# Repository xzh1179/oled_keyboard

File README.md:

# OLED Keyboard

A custom mechanical keyboard project featuring per-key OLED displays for dynamic legends, status information, and highly personalized layouts.

## Overview

OLED Keyboard is an experimental custom keyboard platform where each key can display its own icon, label, layer state, shortcut, or custom graphics.  
The goal of this project is to explore the intersection of keyboard design, multi-panel display integration, power distribution, and user interaction.

This project combines:

- custom PCB design
- embedded firmware development
- OLED display integration
- keyboard matrix scanning
- USB communication
- dynamic key rendering

Depending on the firmware mode, each key can show:

- key labels
- shortcuts
- symbols
- macros
- layer indicators
- application-specific legends
- simple animations or status feedback

## Motivation

Traditional keyboards are static: the legend printed on a keycap never changes.  
This project explores a more flexible and expressive approach where each key can adapt visually to:

- active layer
- language layout
- software context
- macro profile
- user preferences

The idea is to make a keyboard that is not only functional, but also programmable, informative, and visually unique.

## Features

- Per-key OLED displays
- Fully custom PCB
- Mechanical key switches
- Dynamic legends and layer indication
- Custom embedded firmware
- USB connectivity
- Macro and shortcut support
- Potential support for animations and contextual UI

## Hardware

Current hardware exploration includes:

- microcontroller: RP2040 
- OLED display 0.64inch 64x64 pixels, RGB color, based on SSD1357 controller 
- keyboard matrix scanning
- Kailh Choc V1 mechanical switch
- power distribution for many small displays
- SPI display communication
- optional rotary encoder support
- USB interface

> The exact hardware architecture may evolve as the project progresses.

## Architecture

The project is roughly divided into the following blocks:

1. **Keyboard matrix**  
   Detects key presses using rows and columns.

2. **Display subsystem**  
   Drives the OLED displays and refreshes per-key content.

3. **Firmware layer engine**  
   Handles keymaps, layers, macros, and display content generation.

4. **USB HID interface**  
   Sends keyboard events to the host computer.

5. **Power management**  
   Ensures stable power delivery for the MCU, switches, and all displays.

## Challenges

This project involves several interesting engineering challenges:

- driving many OLED displays efficiently
- balancing refresh rate and power consumption
- routing high-density display interconnects on PCB while keeping the layout compact, especially do not create too large space between two keys
- scaling SPI/I2C buses
- memory usage for icons/fonts/framebuffers
- firmware architecture for real-time input + rendering
- mechanical integration and assembly

## Project Status

This project is currently in active development.

Current focus areas include:

- hardware architecture exploration
- PCB design
- display driving strategy
- firmware prototyping
- validation of power and signal integrity constraints

## Repository Structure

```text
.
├── docs/            # Design notes, architecture, ideas, references
├── hardware/        # Schematics, PCB files, manufacturing outputs
├── firmware/        # Embedded firmware source code
├── images/          # Photos, renders, screenshots, diagrams
├── tools/           # Helper scripts, generators, utilities
└── README.md
```

## Assembly
The initial assembly of the keyboard is shown in the two figures below. At this stage, only one screen and one mechanical switch were mounted 
in order to validate the basic functionalities before proceeding with the soldering of the remaining components.

Initial assembly has been completed. Functional testing will be conducted in the next stage.

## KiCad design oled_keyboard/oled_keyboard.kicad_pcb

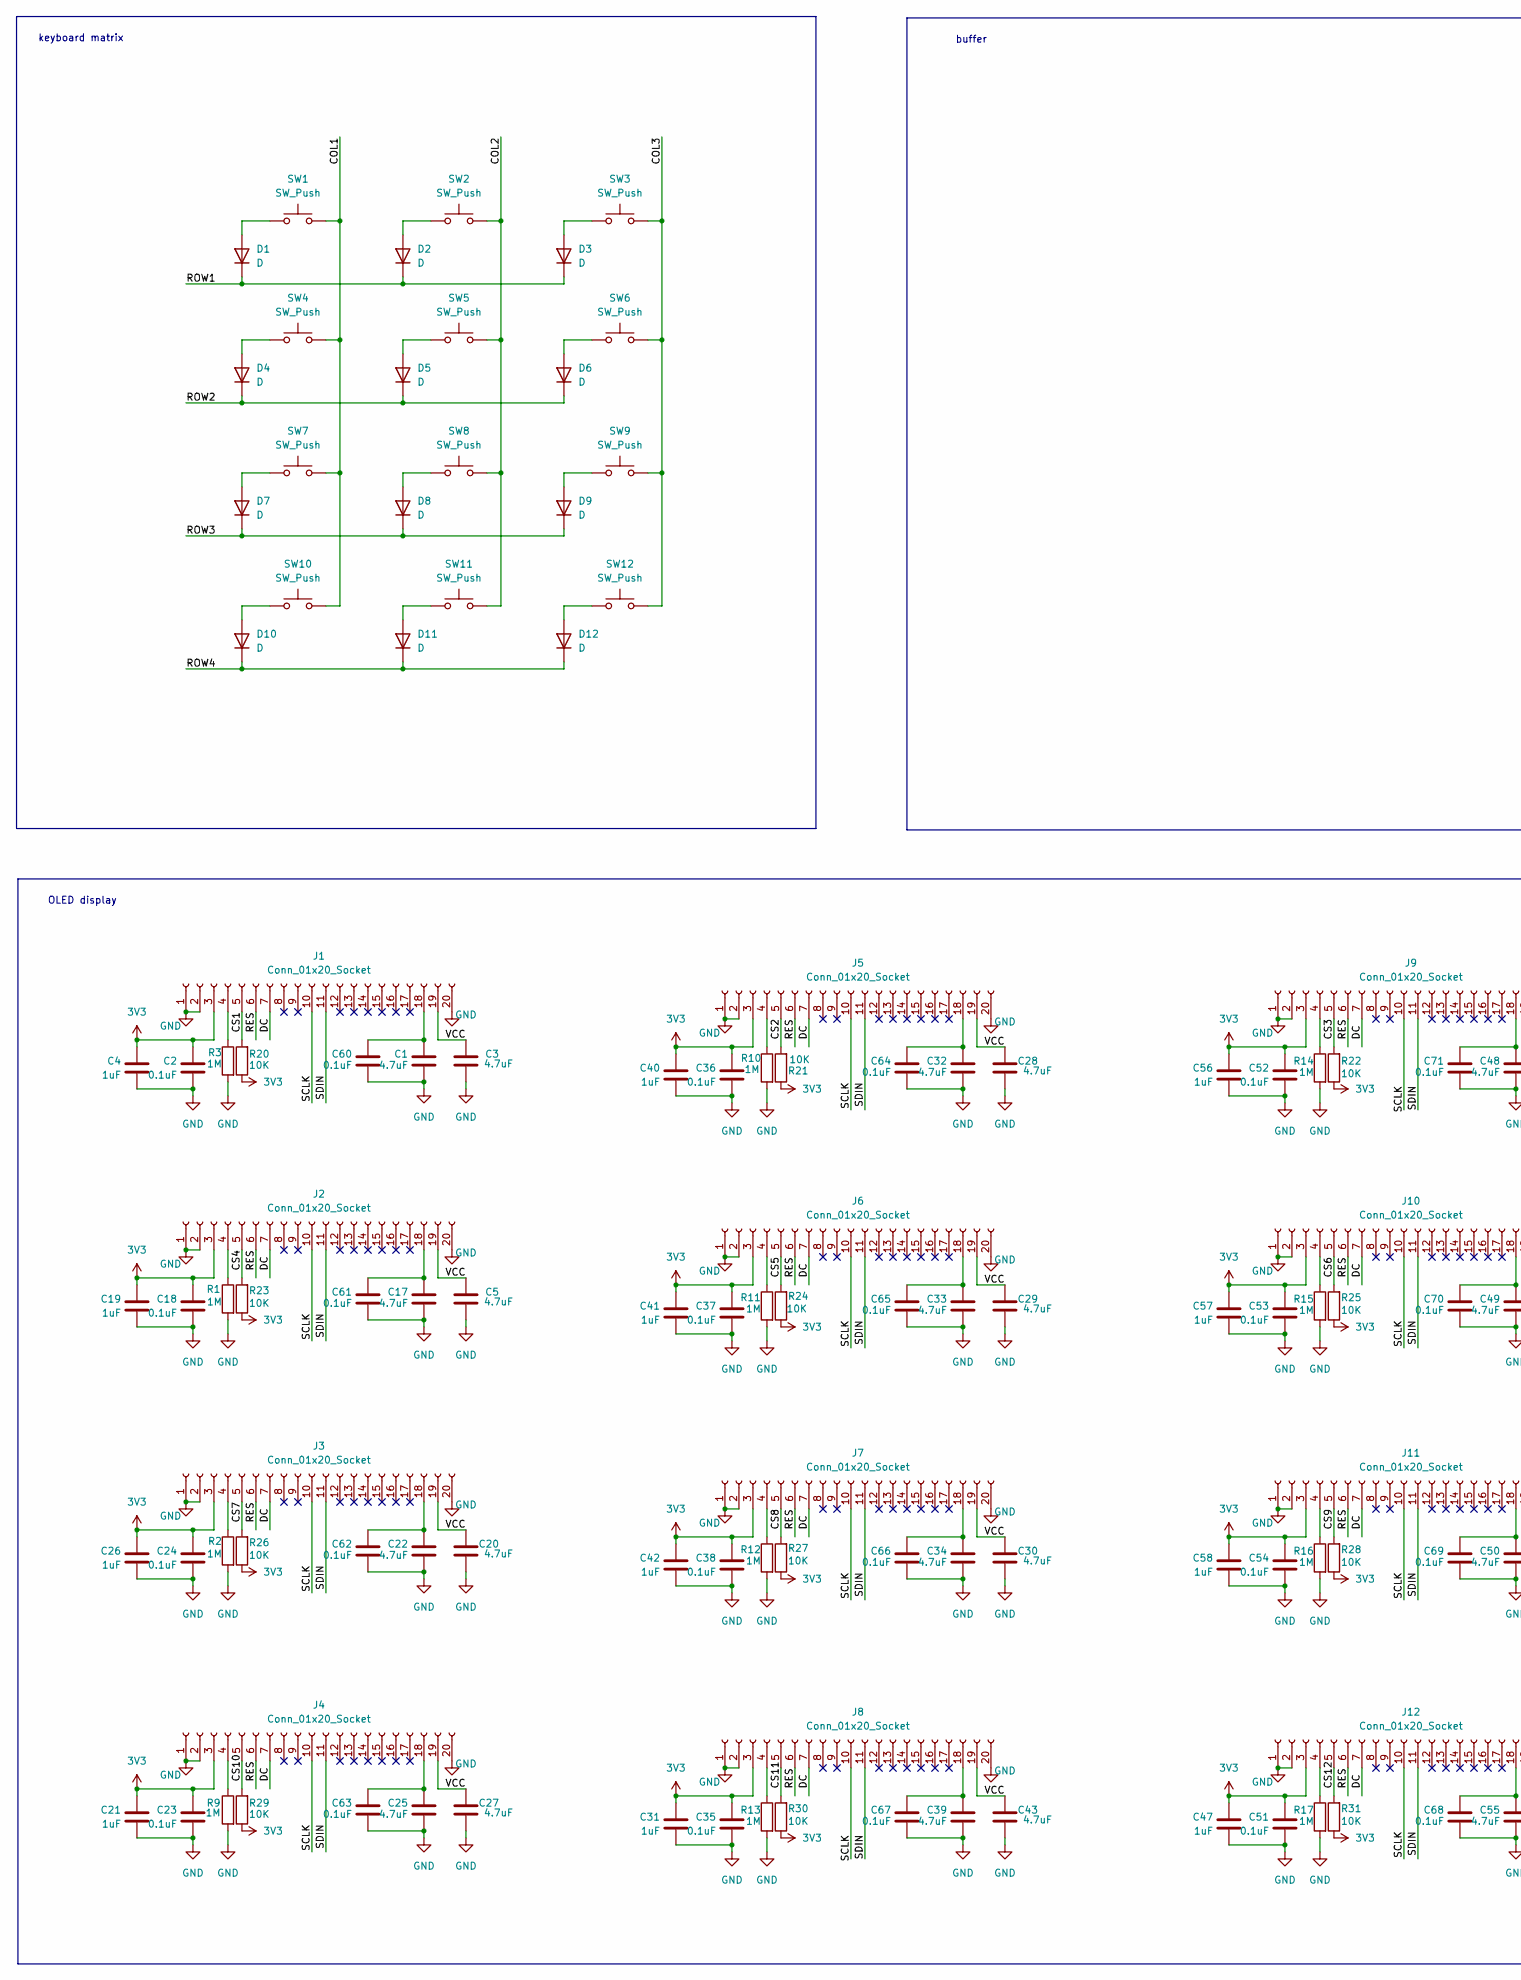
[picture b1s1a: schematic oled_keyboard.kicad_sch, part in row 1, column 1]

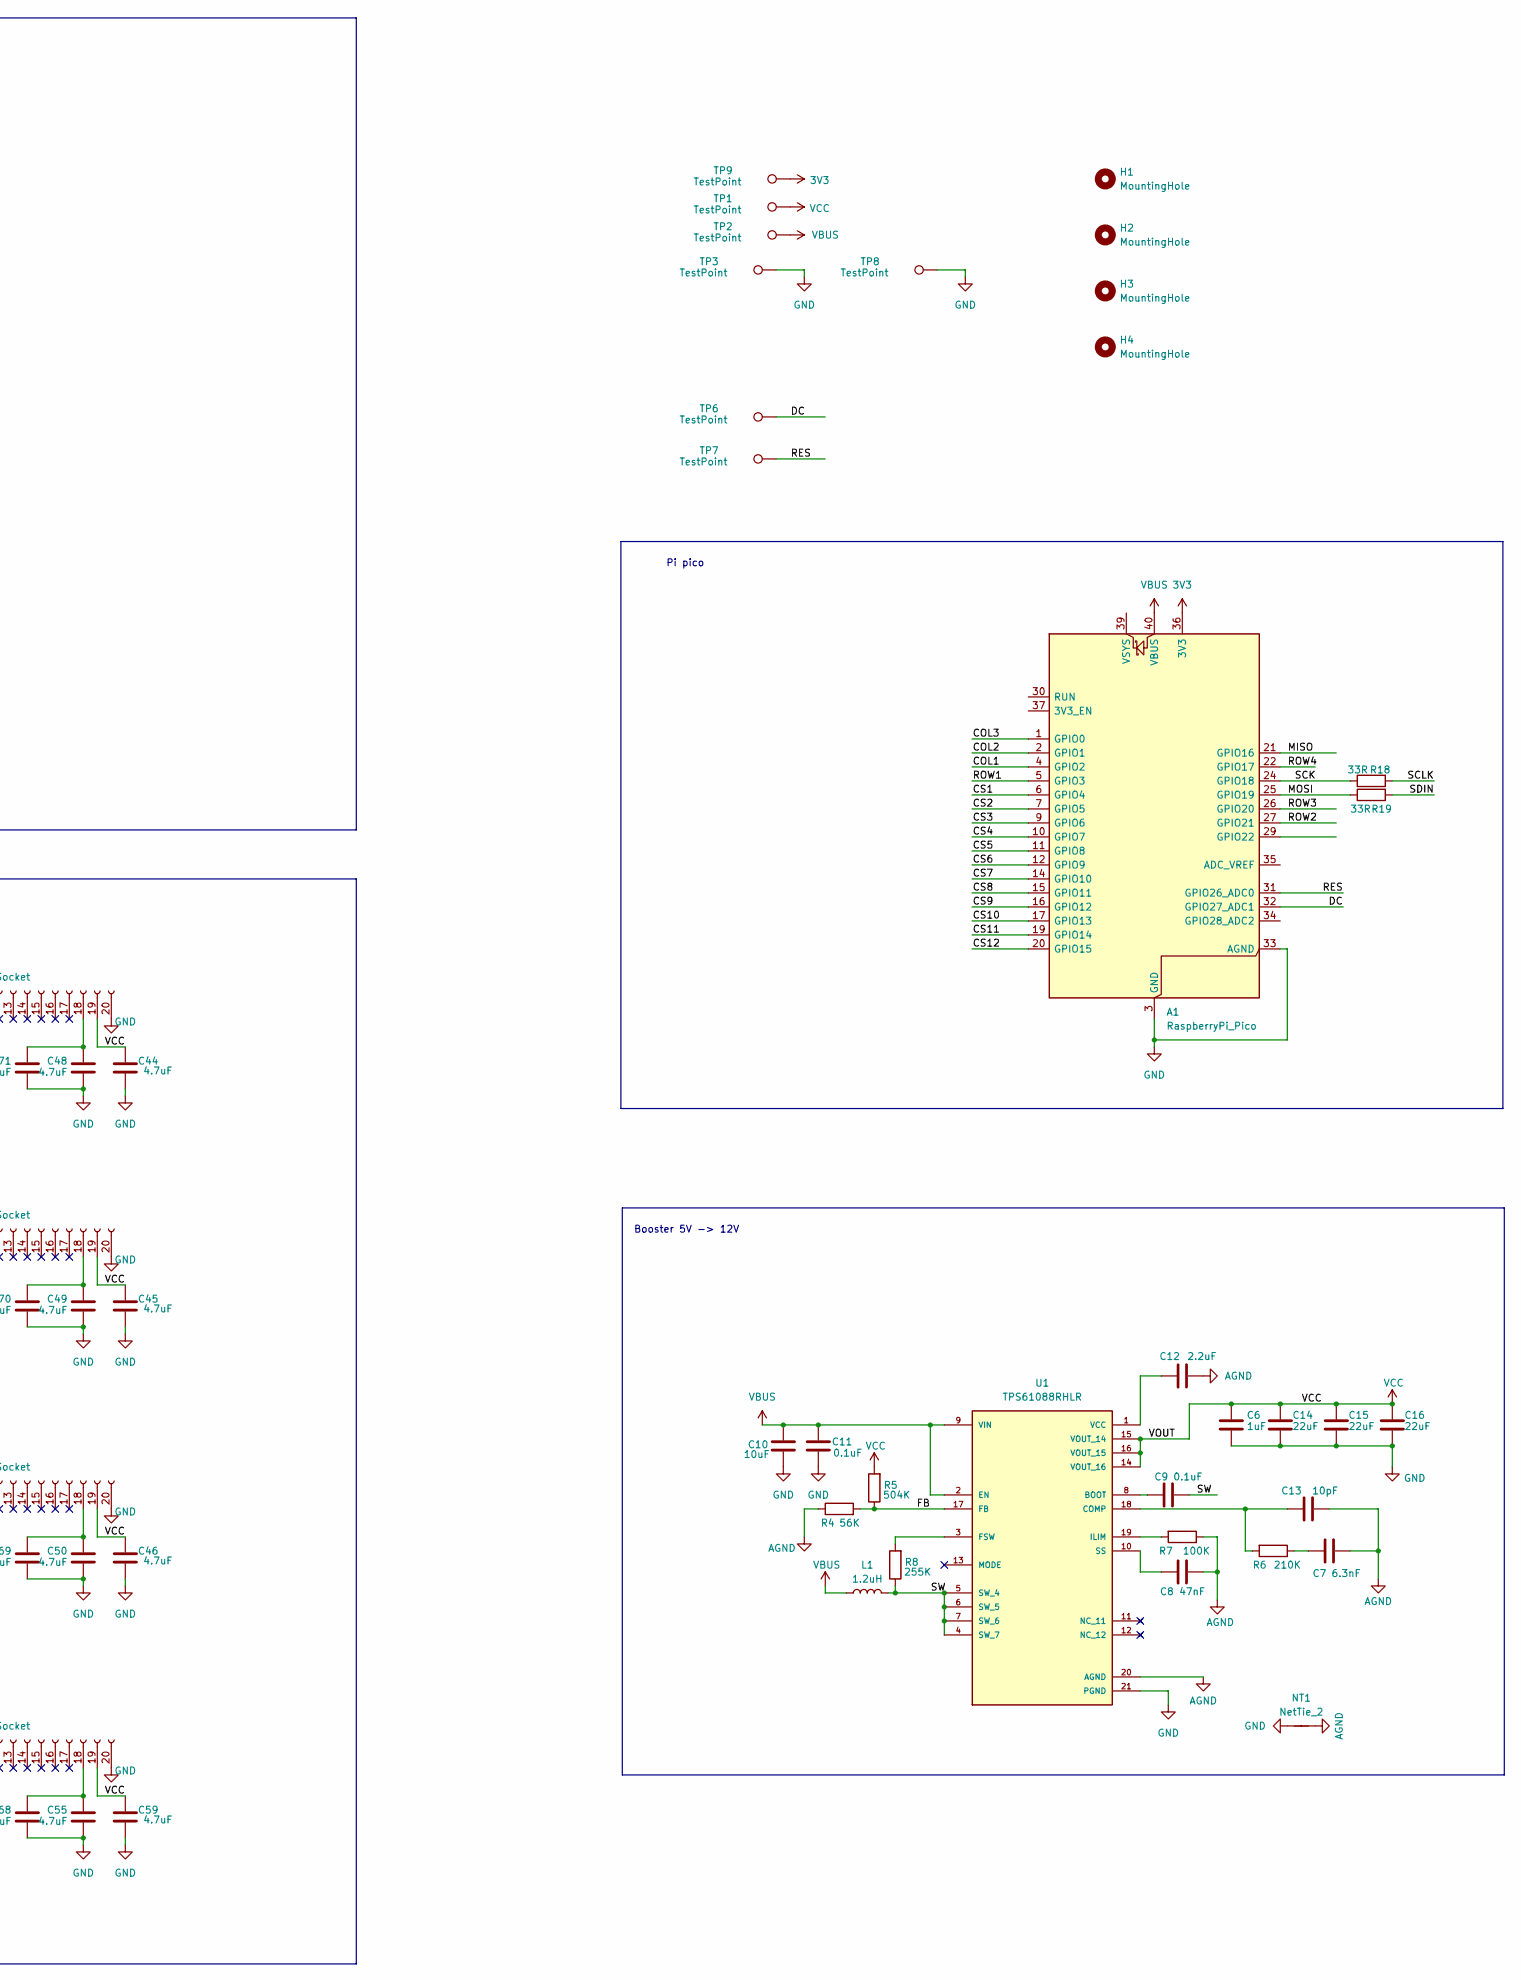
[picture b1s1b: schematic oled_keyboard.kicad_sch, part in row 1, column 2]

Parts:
A1: RaspberryPi_Pico; RaspberryPi_Pico_Common_Unspecified
C1, C3, C5, C17, C20, C22, C25, C27, C28, C29, C30, C32, C33, C34, C39, C43, C44, C45, C46, C48, C49, C50, C55, C59: 4.7uF; C_0603_1608Metric
C2, C9, C11, C18, C23, C24, C35, C36, C37, C38, C51, C52, C53, C54, C60, C61, C62, C63, C64, C65, C66, C67, C68, C69, C70, C71: 0.1uF; C_0603_1608Metric
C4, C6, C19, C21, C26, C31, C40, C41, C42, C47, C56, C57, C58: 1uF; C_0603_1608Metric
C7: 6.3nF; C_0603_1608Metric
C8: 47nF; C_0603_1608Metric
C10: 10uF; C_0603_1608Metric
C12: 2.2uF; C_0603_1608Metric
C13: 10pF; C_0603_1608Metric
C14, C15, C16: 22uF; C_1206_3216Metric
D1, D2, D3, D4, D5, D6, D7, D8, D9, D10, D11, D12: D; D_SOD-123F
H1, H2, H3, H4: MountingHole; MountingHole_2.7mm_M2.5
J1, J2, J3, J4, J5, J6, J7, J8, J9, J10, J11, J12: Conn_01x20_Socket; TE_2-1734742-0
L1: 1.2uH; L_Taiyo-Yuden_MD-4040
NT1: NetTie_2; NetTie-2_SMD_Pad0.5mm
R1, R2, R3, R9, R10, R11, R12, R13, R14, R15, R16, R17: 1M; R_0603_1608Metric
R4: 56K; R_0603_1608Metric
R5: 504K; R_0603_1608Metric
R6: 210K; R_0603_1608Metric
R7: 100K; R_0603_1608Metric
R8: 255K; R_0603_1608Metric
R18, R19: 33R; R_0603_1608Metric
R20, R21, R22, R23, R24, R25, R26, R27, R28, R29, R30, R31: 10K; R_0603_1608Metric
SW1, SW2, SW3, SW4, SW5, SW6, SW7, SW8, SW9, SW10, SW11, SW12: SW_Push; SW_Kailh_Choc_V1V2
TP1, TP2, TP3, TP6, TP7, TP8, TP9: TestPoint; TestPoint_Pad_D2.5mm
U1: TPS61088RHLR; IC_TPS61088RHLR; PARTREV 4219071/A 05/2017

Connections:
3V3: A1.36 (3V3), C2.1, C4.1, C18.1, C19.1, C21.1, C23.1, C24.1, C26.1, C31.1, C35.1, C36.1, C37.1, C38.1, C40.1, C41.1, C42.1, C47.1, C51.1, C52.1, C53.1, C54.1, C56.1, C57.1, C58.1, J1.3, J2.3, J3.3, J4.3, J5.3, J6.3, J7.3, J8.3, J9.3, J10.3, J11.3, J12.3, R20.1, R21.1, R22.1, R23.1, R24.1, R25.1, R26.1, R27.1, R28.1, R29.1, R30.1, R31.1, TP9.1 (1_1)
/COL1: A1.4 (GPIO2), SW1.2, SW4.2, SW7.2, SW10.2
/COL2: A1.2 (GPIO1), SW2.2, SW5.2, SW8.2, SW11.2
/COL3: A1.1 (GPIO0), SW3.2, SW6.2, SW9.2, SW12.2
/CS1: A1.6 (GPIO4), J1.5, R20.2
/CS2: A1.7 (GPIO5), J5.5, R21.2
/CS3: A1.9 (GPIO6), J9.5, R22.2
/CS4: A1.10 (GPIO7), J2.5, R23.2
/CS5: A1.11 (GPIO8), J6.5, R24.2
/CS6: A1.12 (GPIO9), J10.5, R25.2
/CS7: A1.14 (GPIO10), J3.5, R26.2
/CS8: A1.15 (GPIO11), J7.5, R27.2
/CS9: A1.16 (GPIO12), J11.5, R28.2
/CS10: A1.17 (GPIO13), J4.5, R29.2
/CS11: A1.19 (GPIO14), J8.5, R30.2
/CS12: A1.20 (GPIO15), J12.5, R31.2
/DC: A1.32 (GPIO27_ADC1), J1.7, J2.7, J3.7, J4.7, J5.7, J6.7, J7.7, J8.7, J9.7, J10.7, J11.7, J12.7, TP6.1 (1_1)
/FB: R4.2, R5.1, U1.17 (FB)
/MISO: A1.21 (GPIO16)
/MOSI: A1.25 (GPIO19), R19.1
/RES: A1.31 (GPIO26_ADC0), J1.6, J2.6, J3.6, J4.6, J5.6, J6.6, J7.6, J8.6, J9.6, J10.6, J11.6, J12.6, TP7.1 (1_1)
/ROW1: A1.5 (GPIO3), D1.1 (K), D2.1 (K), D3.1 (K)
/ROW2: A1.27 (GPIO21), D4.1 (K), D5.1 (K), D6.1 (K)
/ROW3: A1.26 (GPIO20), D7.1 (K), D8.1 (K), D9.1 (K)
/ROW4: A1.22 (GPIO17), D10.1 (K), D11.1 (K), D12.1 (K)
/SCK: A1.24 (GPIO18), R18.1
/SCLK: J1.10, J2.10, J3.10, J4.10, J5.10, J6.10, J7.10, J8.10, J9.10, J10.10, J11.10, J12.10, R18.2
/SDIN: J1.11, J2.11, J3.11, J4.11, J5.11, J6.11, J7.11, J8.11, J9.11, J10.11, J11.11, J12.11, R19.2
/SW: C9.2, L1.2, R8.1, U1.4 (SW_7), U1.5 (SW_4), U1.6 (SW_5), U1.7 (SW_6)
AGND: C7.2, C8.2, C12.2, C13.2, NT1.1, R4.1, R7.1, U1.20 (AGND)
GND: A1.3 (GND), A1.8 (GND), A1.13 (GND), A1.18 (GND), A1.23 (GND), A1.28 (GND), A1.33 (AGND), A1.38 (GND), C1.2, C2.2, C3.2, C4.2, C5.2, C6.2, C10.1, C11.1, C14.2, C15.2, C16.2, C17.2, C18.2, C19.2, C20.2, C21.2, C22.2, C23.2, C24.2, C25.2, C26.2, C27.2, C28.2, C29.2, C30.2, C31.2, C32.2, C33.2, C34.2, C35.2, C36.2, C37.2, C38.2, C39.2, C40.2, C41.2, C42.2, C43.2, C44.2, C45.2, C46.2, C47.2, C48.2, C49.2, C50.2, C51.2, C52.2, C53.2, C54.2, C55.2, C56.2, C57.2, C58.2, C59.2, C60.2, C61.2, C62.2, C63.2, C64.2, C65.2, C66.2, C67.2, C68.2, C69.2, C70.2, C71.2, J1.1, J1.2, J1.20, J2.1, J2.2, J2.20, J3.1, J3.2, J3.20, J4.1, J4.2, J4.20, J5.1, J5.2, J5.20, J6.1, J6.2, J6.20, J7.1, J7.2, J7.20, J8.1, J8.2, J8.20, J9.1, J9.2, J9.20, J10.1, J10.2, J10.20, J11.1, J11.2, J11.20, J12.1, J12.2, J12.20, NT1.2, R1.2, R2.2, R3.2, R9.2, R10.2, R11.2, R12.2, R13.2, R14.2, R15.2, R16.2, R17.2, TP3.1 (1_1), TP8.1 (1_1), U1.21 (PGND), U1.22 (PGND), U1.23 (PGND), U1.24 (PGND), U1.25 (PGND), U1.26 (PGND), U1.27 (PGND), U1.28 (PGND), U1.29 (PGND)
unnamed: C7.1, R6.1
unnamed: D1.2 (A), SW1.1
unnamed: D2.2 (A), SW2.1
unnamed: D3.2 (A), SW3.1
unnamed: D4.2 (A), SW4.1
unnamed: D5.2 (A), SW5.1
unnamed: D6.2 (A), SW6.1
unnamed: D7.2 (A), SW7.1
unnamed: D8.2 (A), SW8.1
unnamed: D9.2 (A), SW9.1
unnamed: D10.2 (A), SW10.1
unnamed: D11.2 (A), SW11.1
unnamed: D12.2 (A), SW12.1
unnamed: J1.4, R3.1
unnamed: C1.1, C60.1, J1.18
unnamed: J2.4, R1.1
unnamed: C17.1, C61.1, J2.18
unnamed: J3.4, R2.1
unnamed: C22.1, C62.1, J3.18
unnamed: J4.4, R9.1
unnamed: C25.1, C63.1, J4.18
unnamed: J5.4, R10.1
unnamed: C32.1, C64.1, J5.18
unnamed: J6.4, R11.1
unnamed: C33.1, C65.1, J6.18
unnamed: J7.4, R12.1
unnamed: C34.1, C66.1, J7.18
unnamed: J8.4, R13.1
unnamed: C39.1, C67.1, J8.18
unnamed: J9.4, R14.1
unnamed: C48.1, C71.1, J9.18
unnamed: J10.4, R15.1
unnamed: C49.1, C70.1, J10.18
unnamed: J11.4, R16.1
unnamed: C50.1, C69.1, J11.18
unnamed: J12.4, R17.1
unnamed: C55.1, C68.1, J12.18
unnamed: C9.1, U1.8 (BOOT)
unnamed: C13.1, R6.2, U1.18 (COMP)
unnamed: R8.2, U1.3 (FSW)
unnamed: R7.2, U1.19 (ILIM)
unnamed: C8.1, U1.10 (SS)
unnamed: C12.1, U1.1 (VCC)
VBUS: A1.40 (VBUS), C10.2, C11.2, L1.1, TP2.1 (1_1), U1.2 (EN), U1.9 (VIN)
VCC: C3.1, C5.1, C6.1, C14.1, C15.1, C16.1, C20.1, C27.1, C28.1, C29.1, C30.1, C43.1, C44.1, C45.1, C46.1, C59.1, J1.19, J2.19, J3.19, J4.19, J5.19, J6.19, J7.19, J8.19, J9.19, J10.19, J11.19, J12.19, R5.2, TP1.1 (1_1), U1.14 (VOUT_16), U1.15 (VOUT_14), U1.16 (VOUT_15)

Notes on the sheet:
buffer
OLED display
Pi pico
Booster 5V -> 12V
keyboard matrix

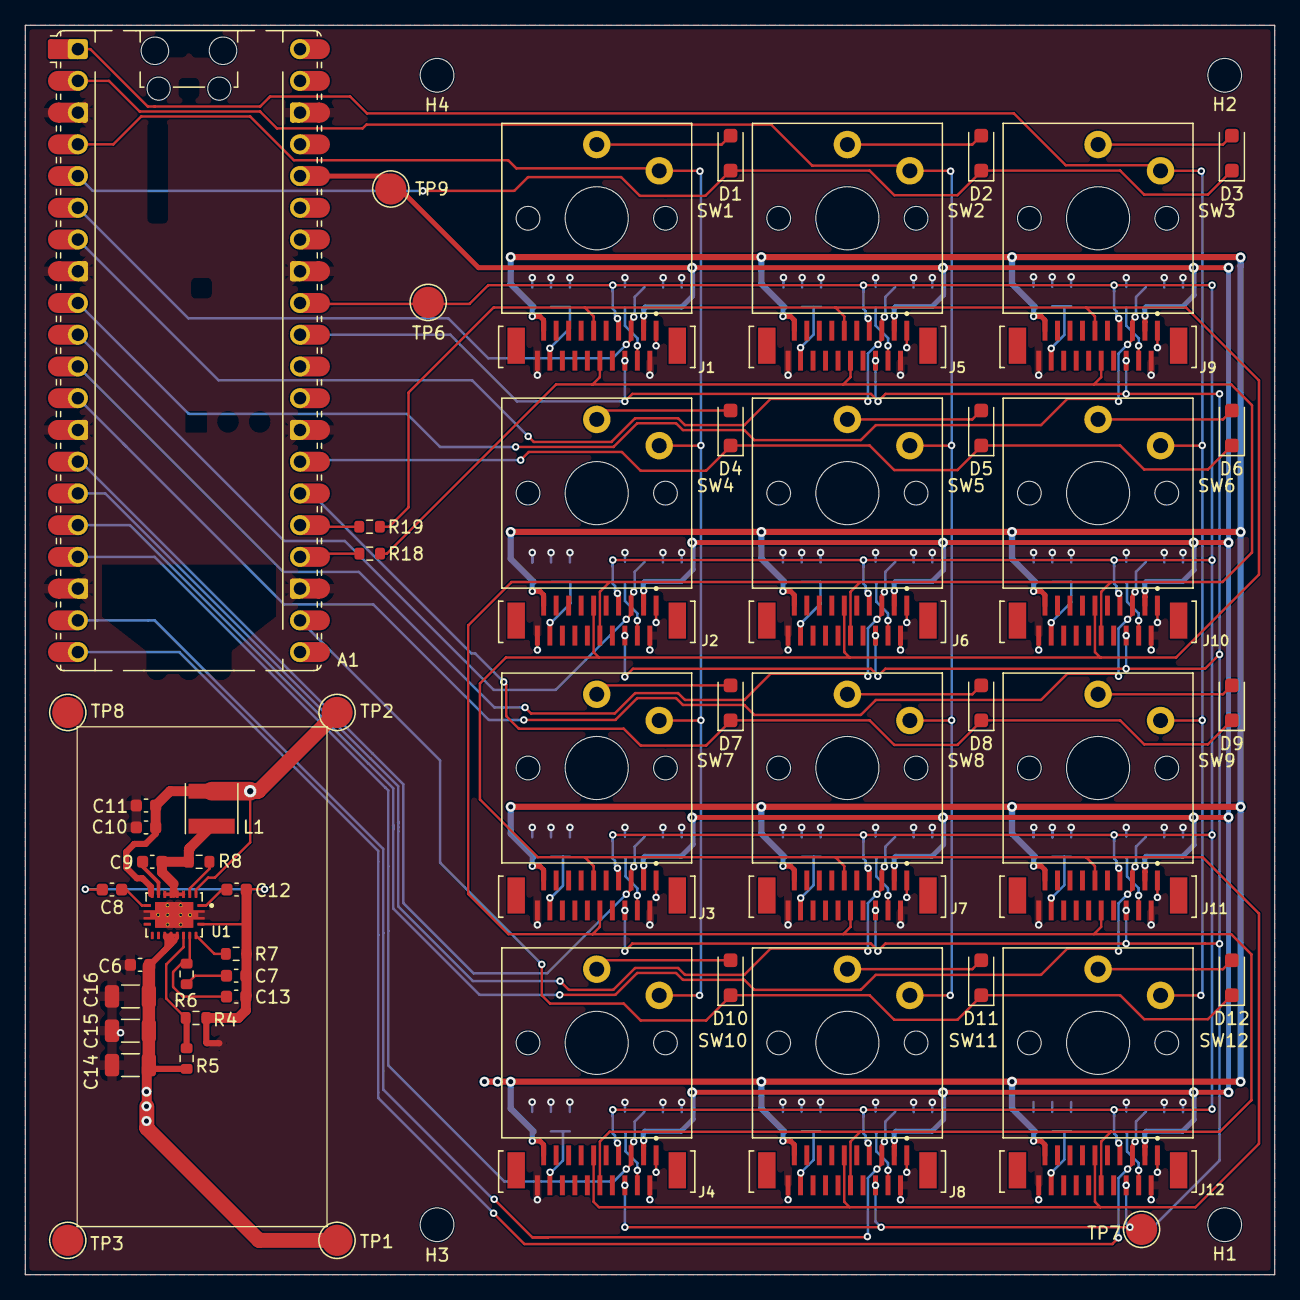
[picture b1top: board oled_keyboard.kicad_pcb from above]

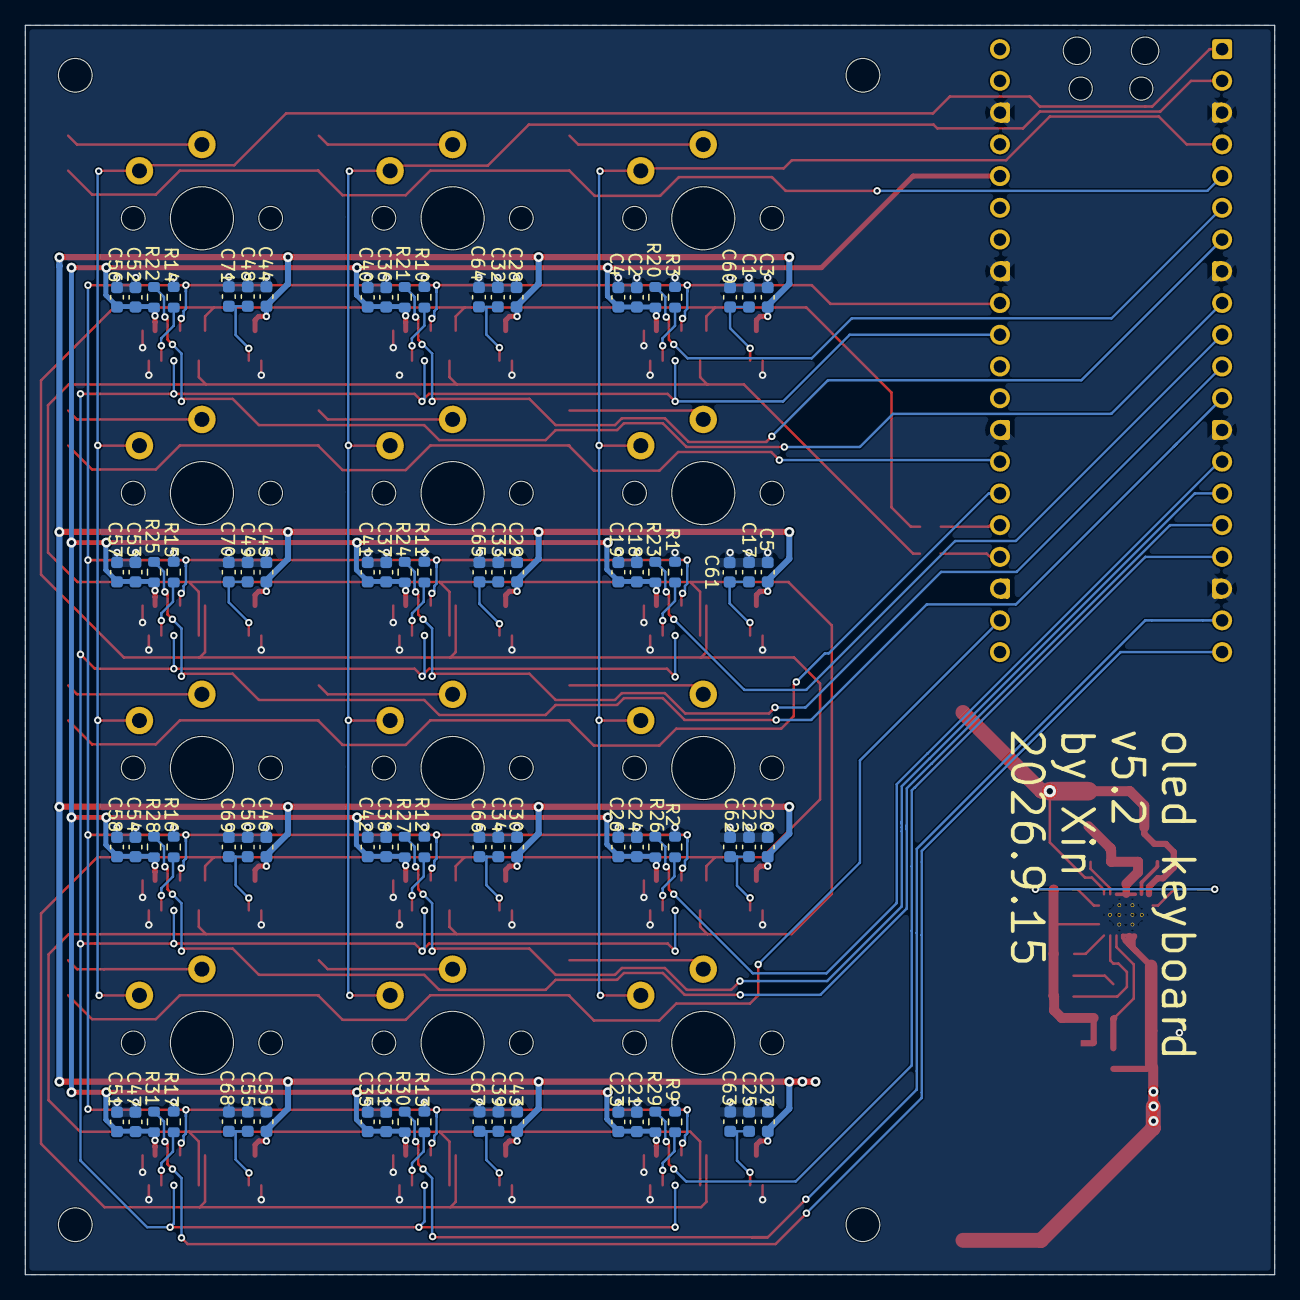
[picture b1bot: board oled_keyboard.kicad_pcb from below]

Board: 4 copper layers, 100.0 x 100.0 mm, 153 parts (84 on the bottom side), 75 nets.

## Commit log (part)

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2026-03-01 routing in progress
2026-03-01 routing ok. added gitignore
2026-03-03 adjusted silkscreen
2026-03-03 added test points
2026-03-07 Initialize README with project overview and features
    Add detailed project description and structure
2026-03-28 fix: fixed reversed 20pin connector pinout
2026-05-24 chged to 9 oled. fixed pin inversion issue
2026-05-25 optimized key layout
2026-05-26 v4.0
2026-06-23 v3.0
2026-06-23 fix: added 3v3! enlarged holes for passing naps
2026-06-23 released v3.1
